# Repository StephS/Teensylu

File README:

UPDATE: TeensyluV1 is a complete redesign of the board. I have moved the power connector closer to the mosfets. Pins have changed! This new board is slightly larger than the older versions - It now matches the size of the Teensylu2
The hotend and bed connectors have changed to high power connectors. The main power connector can either be  screw connector, or a 6-Pin ATX-PCIE power connector. Please note the orientation of the connector and the polarity! Do not use the older 4 pin ATX connector!!!
It is highly recommended that this board is built using 2oz-in copper. Less than that may lead to board damage or FIRE!
I recommend a 15 Amp fuse in the mini-blade fuse holder.

I do not recommend using the older teensylu boards, get the TeensyluV1 board and use the added safety features.

I have decided to release 2 different versions of the board, The 2 Layer version, and 4 Layer version. The 4 layer version has greater power capacity due to uninterrupted power planes. The 2 layer version will be cheaper to manufacture. Functionally the boards are identical. I would prefer the 4 layer version, but I realize that COST is a major issue (up to 3 times the cost to manufacture 4 layer versus 2 layer).

As with all hobbiest electronics, there is a certain degree of risk involved. I had hoped that by making this project open source, that users would provide feedback and improvements to the design.
This has not happened.

Again, Use this board at your own risk!
I am releasing these designs without warranty or guarantee.

There is no such thing as a "Safe" 3d printer controller. Keep a smoke detector nearby and have a fire extinguisher handy. Do NOT the leave unattended. Disconnect from power source when not in use.

http://reprap.org/wiki/Teensylu

If you'd like to donate so I can buy the full version of Eagle, and make more cool stuff, please contact me through Google+ at https://plus.google.com/+StephanieS3D

Disclaimer:
These designs are provided without any warrenty, expressed or implied. This is a prototype designed for hobbiest use only.
Care should be taken during use and appropriate safety precautions taken.
The author is providing this item "as is". The author does not provide any warranty of the item whatsoever, whether express, implied, or statutory, including, but not limited to, any warranty of merchantability or fitness for a particular purpose or any warranty that the contents of the item will be error-free.
In no respect shall the author incur any liability for any damages, including, but limited to, direct, indirect, special, or consequential damages arising out of, resulting from, or any way connected to the use of the item, whether or not based upon warranty, contract, tort, or otherwise; whether or not injury was sustained by persons or property or otherwise; and whether or not loss was sustained from, or arose out of, the results of, the item, or any services that may be provided by the author.

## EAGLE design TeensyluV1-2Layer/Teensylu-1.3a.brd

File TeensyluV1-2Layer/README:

Version 1.3 is ready for production, earlier versions should not be used.
This version is a 2 Layer board designed for low cost manufacturing. A 4 Layer board is also available.
It is required that the top and bottom layers be 2oz/in.
24v power supply should be possible, please note to use a 24v heat bed, hotend, and fans or else damage or FIRE can occur.

Assembly notes:
J1-J7 are 22ga Solid core wire jumpers at 0.1" spacing. Do not attempt to stuff with headers.
J13 and J15 occupy the same space. Choose an appropriate header for the target system.

Please see TeensyluV1_Pin_Mapping.txt for the correct pin mapping using the teensyduino library. Analog pins should use the analog pin reference.

The BOM is included. Please use parts of the same or higher ratings.

If you'd like to donate so I can buy the full version of Eagle, and make more cool stuff, please contact me through Google+ at https://plus.google.com/+StephanieS3D

Disclaimer:
These designs are provided without any warrenty, expressed or implied. This is a prototype designed for hobbiest use only.
Care should be taken during use and appropriate safety precautions taken.
The author is providing this item "as is". The author does not provide any warranty of the item whatsoever, whether express, implied, or statutory, including, but not limited to, any warranty of merchantability or fitness for a particular purpose or any warranty that the contents of the item will be error-free.
In no respect shall the author incur any liability for any damages, including, but limited to, direct, indirect, special, or consequential damages arising out of, resulting from, or any way connected to the use of the item, whether or not based upon warranty, contract, tort, or otherwise; whether or not injury was sustained by persons or property or otherwise; and whether or not loss was sustained from, or arose out of, the results of, the item, or any services that may be provided by the author.

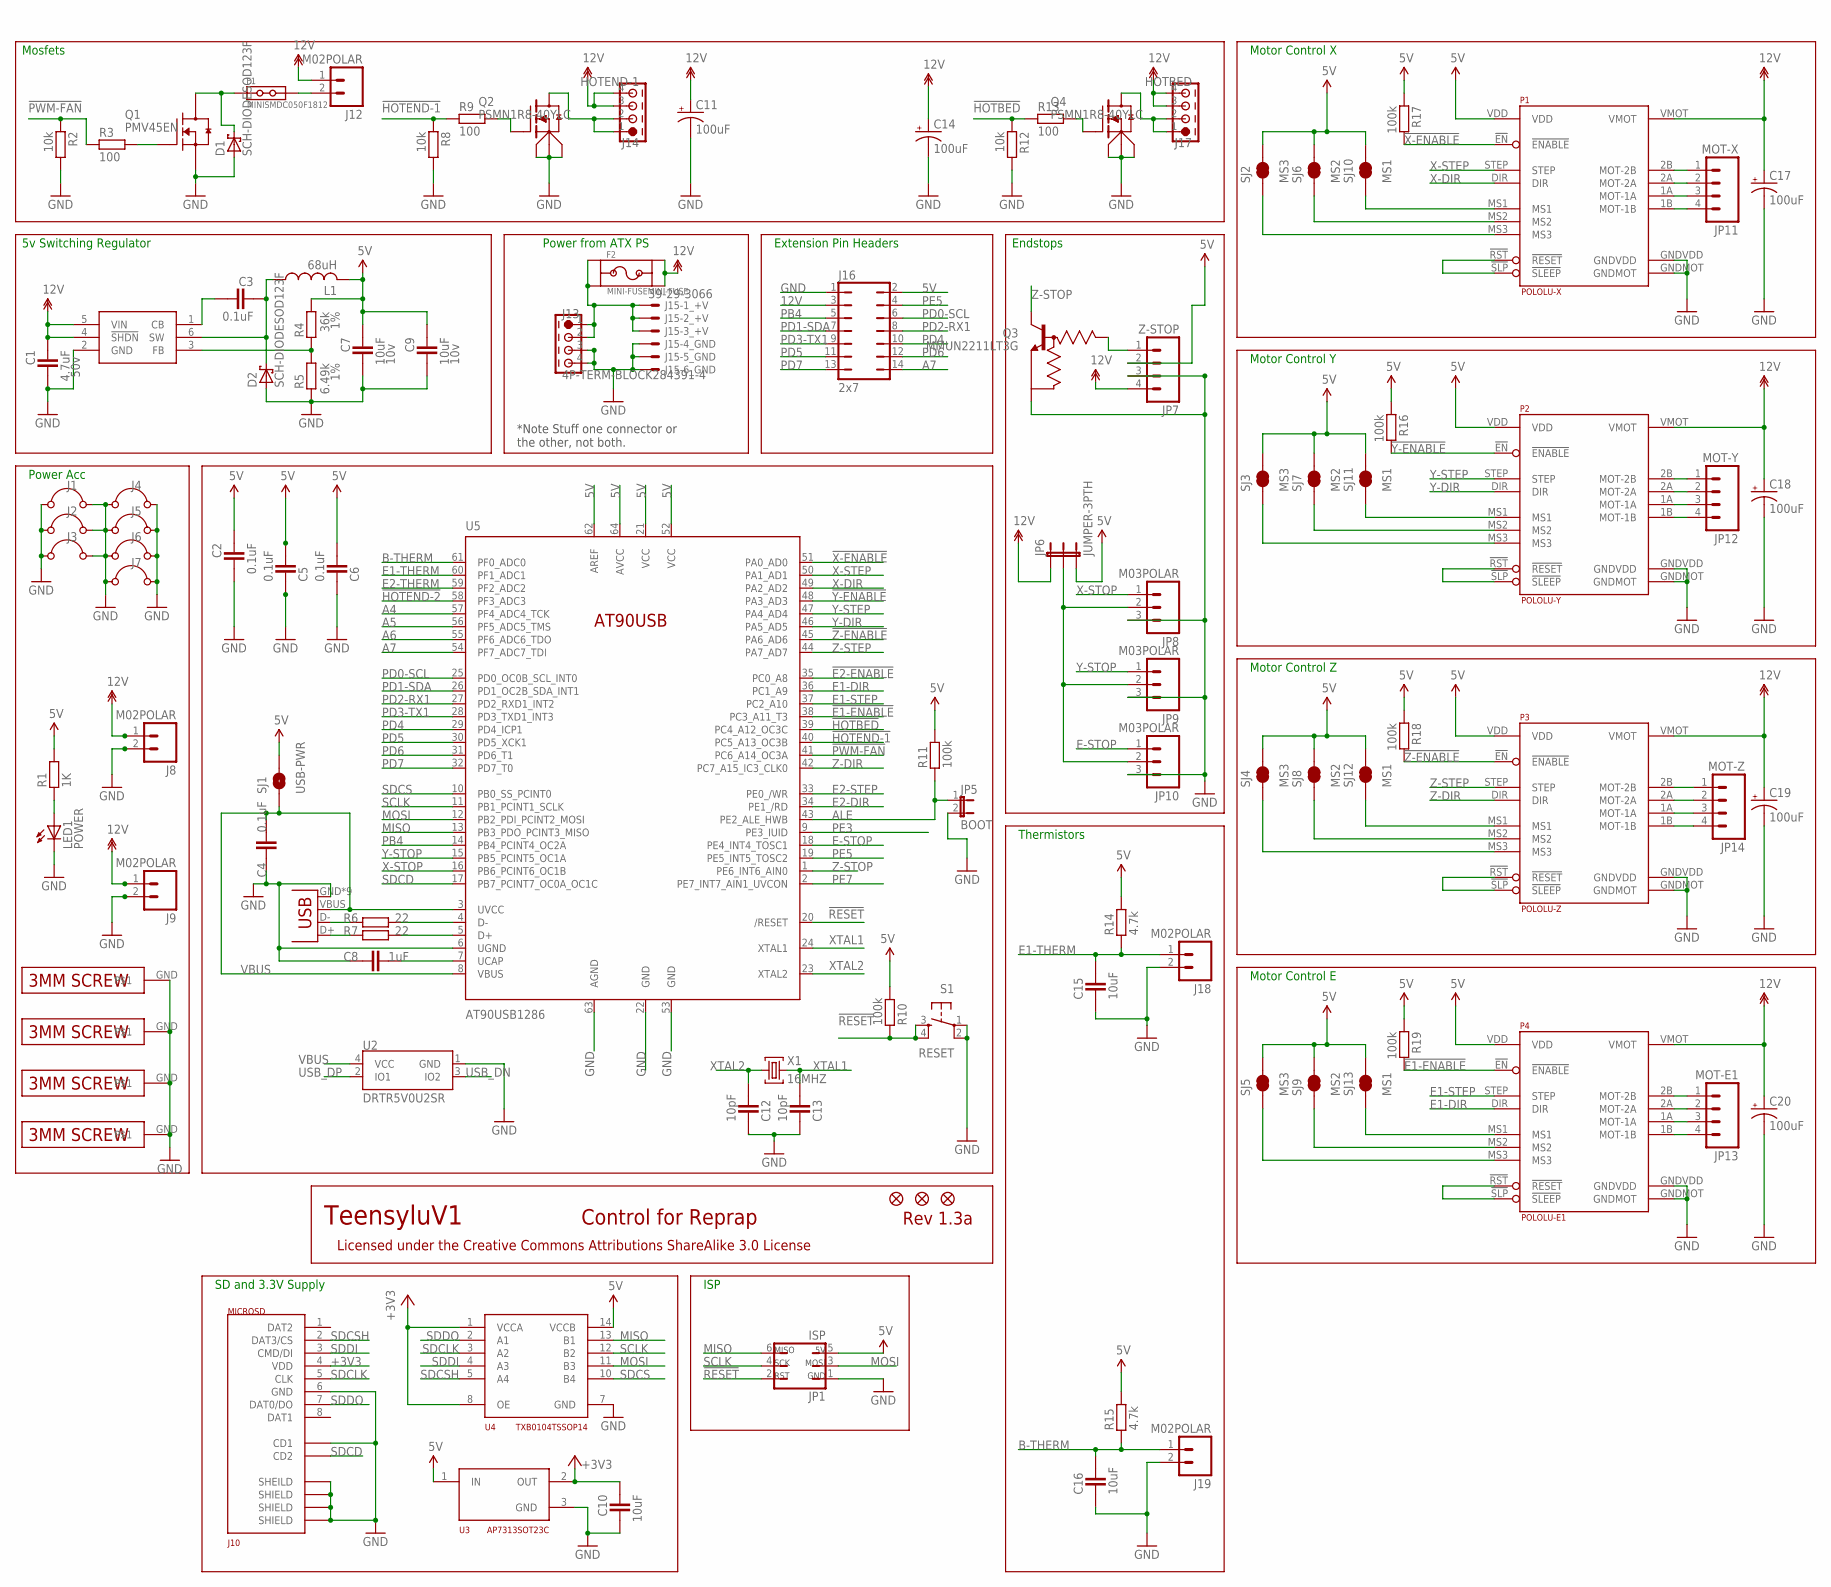
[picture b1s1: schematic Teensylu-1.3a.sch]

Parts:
C1: 4.7uF; CAPC3215X168N; TOLERANCE 10%; MANUFACTURER_PART_NUMBER UMK316AB7475KL-T
C2, C4, C5, C6: 0.1uF; CAPC1608X92N; TOLERANCE 10%; MANUFACTURER_PART_NUMBER GRM188R71C104KA01D
C3: 0.1uF; CAPC1608X92N; TOLERANCE 10%; MANUFACTURER_PART_NUMBER CL10B104KB8NNNC
C7, C9: 10uF; CAPC2012X145AN; TOLERANCE 10%; MANUFACTURER_PART_NUMBER GRM21BR71A106KE51L
C8: 1uF; CAPC1608X92N; TOLERANCE 20%; MANUFACTURER_PART_NUMBER CL10A105MO8NNNC
C10, C15, C16: 10uF; CAPC1608X92N; TOLERANCE 20%; MANUFACTURER_PART_NUMBER GRM188R61C106MA73D
C11, C14, C17, C18, C19, C20: 100uF; PANASONIC_D; TOLERANCE 20%; MANUFACTURER_PART_NUMBER EEE-FTH101XAP
C12, C13: 10pF; CAPC1608X92N; TOLERANCE 5%; MANUFACTURER_PART_NUMBER CL10C100JB8NCNC
D1: SCH-DIODESOD123F; SOD123F
D2: SCH-DIODESOD123F; SOD123F; MANUFACTURER_PART_NUMBER PMEG4010CEH,115
F1: MINISMDC050F1812; MINISMDC
F2: MINI-FUSEMINI-FUSE; MINI_FUSE
J1, J2, J3, J4, J5, J6, J7: 22ga; WJ_01_08; MANUFACTURER_PART_NUMBER N/A
J8, J9, J12, J18, J19: M02POLAR; MOLEX-1X2; MANUFACTURER_PART_NUMBER 0022272021
J10: MICROSD; AMPHENOL-MICROSD
J11: USB-MICRO-PTH; USB-MICROB-PTH
J13: 4P-TERM-BLOCK284391-4; 284391-4
J14: HOTEND-1; 284391-4
J15: 39-29-3066
J16: 2x7; JP7Q; MANUFACTURER_PART_NUMBER M20-9980746
J17: HOTBED; 284391-4
JP1: ISP
JP2, JP3, JP4: FIDUCIAL1X2.5; FIDUCIAL-1X2.5
JP5: BOOT; 1X02; MANUFACTURER_PART_NUMBER M20-9990246
JP6: JUMPER-3PTH; 1X03
JP7: Z-STOP; MOLEX-1X4
JP8, JP9, JP10: M03POLAR; MOLEX-1X3; MANUFACTURER_PART_NUMBER 0022272031
JP11: MOT-X; MOLEX-1X4
JP12: MOT-Y; MOLEX-1X4
JP13: MOT-E1; MOLEX-1X4
JP14: MOT-Z; MOLEX-1X4
L1: 68uH; SRN6045; MANUFACTURER_PART_NUMBER SRN6045-680M
LED1: POWER; CHIPLED_0805; MANUFACTURER_PART_NUMBER APT2012SGC
P1: POLOLU-X; POLOLU-STEPPER-PTH
P2: POLOLU-Y; POLOLU-STEPPER-PTH
P3: POLOLU-Z; POLOLU-STEPPER-PTH
P4: POLOLU-E1; POLOLU-STEPPER-PTH
Q1: PMV45EN; SOT23C; VOLTAGE 60V; MANUFACTURER_PART_NUMBER IRLML2060TRPBF
Q2, Q4: PSMN1R8-40YLC; LFPACK-POWERPAK-SO8
Q3: MMUN2211LT3G; SOT23C; MANUFACTURER_PART_NUMBER MMUN2211LT3G
R1: 1K; RESC1608X55N
R2, R8, R12: 10k; RESC1608X55N
R3, R9, R13: 100; RESC1608X55N
R4: 36k; RESC1608X55N; TOLERANCE 1%
R5: 6.49k; RESC1608X55N; TOLERANCE 1%
R6, R7: 22; RESC1608X55N
R10, R11, R16, R17, R18, R19: 100k; RESC1608X55N
R14, R15: 4.7k; RESC1608X55N
S1: RESET; TACTILE_SWITCH_SMD
SCREW1, SCREW2, SCREW3, SCREW4: 3MM-SCREW; PLATEDSCREW
SJ1: USB-PWR; SJ_2S-NO
SJ2, SJ3, SJ4, SJ5: MS3; SJ_2S-TRACE
SJ6, SJ7, SJ8, SJ9: MS2; SJ_2S-TRACE
SJ10, SJ11, SJ12, SJ13: MS1; SJ_2S-TRACE
U1: LMR16006X; TSOT6
U2: DRTR5V0U2SR; SOT143-R
U3: AP7313SOT23C; SOT23C
U4: TXB0104TSSOP14; TSSOP14
U5: AT90USB1286; TQFP64-2; MANUFACTURER_PART_NUMBER AT90USB1286
X1: 16MHZ; NDK-XTAL; MANUFACTURER_PART_NUMBER NX5032GA-16.000000MHZ-LN-CD-1

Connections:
5V: C2.1, C5.2, C6.2, C7.1, C9.1, J16.2, JP1.5, JP6.3, JP7.2, L1.2, P1.VDD, P2.VDD, P3.VDD, P4.VDD, R1.2, R4.1, R10.2, R11.2, R14.2, R15.2, R16.1, R17.1, R18.1, R19.1, SJ1.2, SJ2.2, SJ3.2, SJ4.2, SJ5.2, SJ6.2, SJ7.2, SJ8.2, SJ9.2, SJ10.2, SJ11.2, SJ12.2, SJ13.2, U3.1 (IN), U4.14 (VCCB), U5.21 (VCC), U5.52 (VCC), U5.62 (AREF), U5.64 (AVCC)
5VREG_CB: C3.2, U1.1 (CB)
5VREG_FB: R4.2, R5.1, U1.3 (FB)
5VREG_SW: C3.1, D2.C, L1.1, U1.6 (SW)
12V: C1.1, C11.+, C14.+, C17.+, C18.+, C19.+, C20.+, F2.P$3, F2.P$4, J8.1, J9.1, J12.1, J14.3, J14.4, J16.3, J17.3, J17.4, JP6.1, JP7.4, P1.VMOT, P2.VMOT, P3.VMOT, P4.VMOT, U1.4 (!SHDN), U1.5 (VIN)
12V_FUSE: F2.P$1, F2.P$2, J13.1, J13.2, J15.1, J15.2, J15.3
!E1-ENABLE: P4.!EN (!ENABLE), R19.2, U5.38 (PC3_A11_T3)
!E2-ENABLE: U5.35 (PC0_A8)
!HOTBED: R12.1, R13.1, U5.39 (PC4_A12_OC3C)
!HOTEND-1: R8.1, R9.1, U5.40 (PC5_A13_OC3B)
!HOTEND-2: U5.58 (PF3_ADC3)
!PWM-FAN: R2.1, R3.1, U5.41 (PC6_A14_OC3A)
!RESET: JP1.2, R10.1, S1.3, S1.4, U5.20 (/RESET)
!X-ENABLE: P1.!EN (!ENABLE), R17.2, U5.51 (PA0_AD0)
!Y-ENABLE: P2.!EN (!ENABLE), R16.2, U5.48 (PA3_AD3)
!Z-ENABLE: P3.!EN (!ENABLE), R18.2, U5.45 (PA6_AD6)
+3V3: C10.1, J10.4 (VDD), U3.2 (OUT), U4.1 (VCCA), U4.8 (OE)
A4: U5.57 (PF4_ADC4_TCK)
A5: U5.56 (PF5_ADC5_TMS)
A6: U5.55 (PF6_ADC6_TDO)
A7: J16.14, U5.54 (PF7_ADC7_TDI)
ALE: JP5.1, R11.1, U5.43 (PE2_ALE_HWB)
B-THERM: C16.2, J19.1, R15.1, U5.61 (PF0_ADC0)
E1-DIR: P4.DIR, U5.36 (PC1_A9)
E1-STEP: P4.STEP, U5.37 (PC2_A10)
E1-THERM: C15.2, J18.1, R14.1, U5.60 (PF1_ADC1)
E2-DIR: U5.34 (PE1_/RD)
E2-STEP: U5.33 (PE0_/WR)
E2-THERM: U5.59 (PF2_ADC2)
E-MOT-1A: JP13.3, P4.1A (MOT-1A)
E-MOT-1B: JP13.4, P4.1B (MOT-1B)
E-MOT-2A: JP13.2, P4.2A (MOT-2A)
E-MOT-2B: JP13.1, P4.2B (MOT-2B)
E-MS1: P4.MS1, SJ13.1
E-MS2: P4.MS2, SJ9.1
E-MS3: P4.MS3, SJ5.1
E-RESETSLEEP: P4.!RST (!RESET), P4.!SLP (!SLEEP)
E-STOP: JP10.1, U5.18 (PE4_INT4_TOSC1)
ENDSTOP+V: JP6.2, JP8.2, JP9.2, JP10.2
GND: C1.2, C2.2, C4.1, C5.1, C6.1, C7.2, C8.1, C9.2, C10.2, C11.-, C12.1, C13.1, C14.-, C15.1, C16.1, C17.-, C18.-, C19.-, C20.-, D1.A, D2.A, J1.1 (+), J1.2 (-), J2.1 (+), J2.2 (-), J3.1 (+), J3.2 (-), J4.1 (+), J4.2 (-), J5.1 (+), J5.2 (-), J6.1 (+), J6.2 (-), J7.1 (+), J7.2 (-), J8.2, J9.2, J10.6 (GND), J10.C1 (SHEILD), J10.C2 (SHIELD), J10.C3 (SHIELD), J10.C4 (SHIELD), J10.CD1, J11.GND, J11.GND1 (GND), J11.GND2 (GND), J11.GND3 (GND), J11.GND4 (GND), J11.GND5 (GND), J11.GND6 (GND), J11.GND7 (GND), J11.GND8 (GND), J13.3, J13.4, J15.4, J15.5, J15.6, J16.1, J18.2, J19.2, JP1.1, JP5.2, JP7.3, JP8.3, JP9.3, JP10.3, LED1.C, P1.GNDMOT, P1.GNDVDD, P2.GNDMOT, P2.GNDVDD, P3.GNDMOT, P3.GNDVDD, P4.GNDMOT, P4.GNDVDD, Q1.2 (S), Q2.1 (S1), Q2.2 (S2), Q2.3 (S3), Q3.2 (E), Q4.1 (S1), Q4.2 (S2), Q4.3 (S3), R2.2, R5.2, R8.2, R12.2, S1.1, S1.2, SCREW1.GND, SCREW2.GND, SCREW3.GND, SCREW4.GND, U1.2 (GND), U2.1 (GND), U3.3 (GND), U4.7 (GND), U5.6 (UGND), U5.22 (GND), U5.53 (GND), U5.63 (AGND)
HOTBED-GND: J17.1, J17.2, Q4.5-8 (D)
HOTEND-GND: J14.1, J14.2, Q2.5-8 (D)
MISO: JP1.6, U4.13 (B1), U5.13 (PB3_PDO_PCINT3_MISO)
MOSI: JP1.3, U4.11 (B3), U5.12 (PB2_PDI_PCINT2_MOSI)
unnamed: LED1.A, R1.1
unnamed: Q4.4 (G), R13.2
unnamed: R6.2, U5.4 (D-)
unnamed: R7.2, U5.5 (D+)
unnamed: F1.P$2, J12.2
unnamed: D1.C, F1.P$1, Q1.3 (D)
unnamed: Q1.1 (G), R3.2
unnamed: Q2.4 (G), R9.2
PB4: J16.5, U5.14 (PB4_PCINT4_OC2A)
PD0-SCL: J16.6, U5.25 (PD0_OC0B_SCL_INT0)
PD1-SDA: J16.7, U5.26 (PD1_OC2B_SDA_INT1)
PD2-RX1: J16.8, U5.27 (PD2_RXD1_INT2)
PD3-TX1: J16.9, U5.28 (PD3_TXD1_INT3)
PD4: J16.10, U5.29 (PD4_ICP1)
PD5: J16.11, U5.30 (PD5_XCK1)
PD6: J16.12, U5.31 (PD6_T1)
PD7: J16.13, U5.32 (PD7_T0)
PE3: U5.9 (PE3_IUID)
PE5: J16.4, U5.19 (PE5_INT5_TOSC2)
PE7: U5.2 (PE7_INT7_AIN1_UVCON)
SCLK: JP1.4, U4.12 (B2), U5.11 (PB1_PCINT1_SCLK)
SDCD: J10.CD2, U5.17 (PB7_PCINT7_OC0A_OC1C)
SDCLK: J10.5 (CLK), U4.3 (A2)
SDCS: U4.10 (B4), U5.10 (PB0_SS_PCINT0)
SDCSH: J10.2 (DAT3/CS), U4.5 (A4)
SDDI: J10.3 (CMD/DI), U4.4 (A3)
SDDO: J10.7 (DAT0/DO), U4.2 (A1)
UCAP: C8.2, U5.7 (UCAP)
USB_DN: J11.D-, R6.1, U2.3 (IO2)
USB_DP: J11.D+, R7.1, U2.2 (IO1)
VBUS: C4.2, J11.VBUS, SJ1.1, U2.4 (VCC), U5.3 (UVCC), U5.8 (VBUS)
X-DIR: P1.DIR, U5.49 (PA2_AD2)
X-MOT-1A: JP11.3, P1.1A (MOT-1A)
X-MOT-1B: JP11.4, P1.1B (MOT-1B)
X-MOT-2A: JP11.2, P1.2A (MOT-2A)
X-MOT-2B: JP11.1, P1.2B (MOT-2B)
X-MS1: P1.MS1, SJ10.1
X-MS2: P1.MS2, SJ6.1
X-MS3: P1.MS3, SJ2.1
X-RESETSLEEP: P1.!RST (!RESET), P1.!SLP (!SLEEP)
X-STEP: P1.STEP, U5.50 (PA1_AD1)
X-STOP: JP8.1, U5.16 (PB6_PCINT6_OC1B)
XTAL1: C13.2, U5.24 (XTAL1), X1.P$2 (2)
XTAL2: C12.2, U5.23 (XTAL2), X1.P$1 (1)
Y-DIR: P2.DIR, U5.46 (PA5_AD5)
Y-MOT-1A: JP12.3, P2.1A (MOT-1A)
Y-MOT-1B: JP12.4, P2.1B (MOT-1B)
Y-MOT-2A: JP12.2, P2.2A (MOT-2A)
Y-MOT-2B: JP12.1, P2.2B (MOT-2B)
Y-MS1: P2.MS1, SJ11.1
Y-MS2: P2.MS2, SJ7.1
Y-MS3: P2.MS3, SJ3.1
Y-RESETSLEEP: P2.!RST (!RESET), P2.!SLP (!SLEEP)
Y-STEP: P2.STEP, U5.47 (PA4_AD4)
Y-STOP: JP9.1, U5.15 (PB5_PCINT5_OC1A)
Z-DIR: P3.DIR, U5.42 (PC7_A15_IC3_CLK0)
Z-MOT-1A: JP14.3, P3.1A (MOT-1A)
Z-MOT-1B: JP14.4, P3.1B (MOT-1B)
Z-MOT-2A: JP14.2, P3.2A (MOT-2A)
Z-MOT-2B: JP14.1, P3.2B (MOT-2B)
Z-MS1: P3.MS1, SJ12.1
Z-MS2: P3.MS2, SJ8.1
Z-MS3: P3.MS3, SJ4.1
Z-RESETSLEEP: P3.!RST (!RESET), P3.!SLP (!SLEEP)
Z-STEP: P3.STEP, U5.44 (PA7_AD7)
Z-STOP: Q3.3 (C), U5.1 (PE6_INT6_AIN0)
Z-STOP-BIAS: JP7.1, Q3.1 (B)

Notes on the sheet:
Motor Control X
Motor Control Y
Motor Control Z
Motor Control E
ISP
Thermistors
Endstops
Mosfets
Power Acc
TeensyluV1
Rev 1.3a
Control for Reprap
Licensed under the Creative Commons Attributions ShareAlike 3.0 License
Extension Pin Headers
Power from ATX PS
5v Switching Regulator
SD and 3.3V Supply
*Note Stuff one connector or the other, not both.

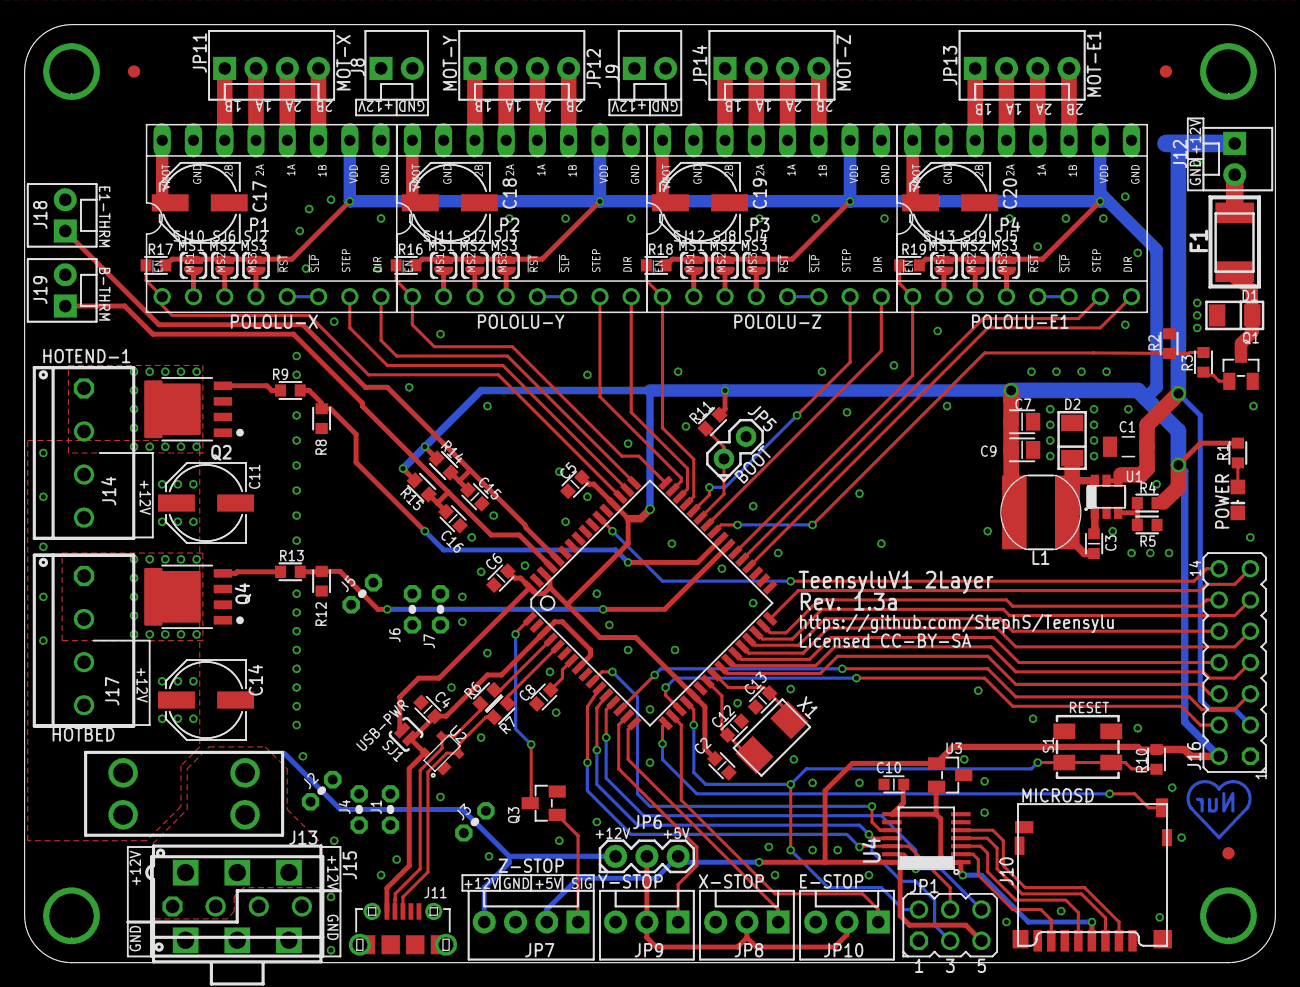
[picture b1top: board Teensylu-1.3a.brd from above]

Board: 2 copper layers, 101.6 x 76.2 mm, 110 parts (0 on the bottom side), 101 nets.

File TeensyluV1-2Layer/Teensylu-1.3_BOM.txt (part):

Part   Value                 Device                     Package             Description                                                                   CURRENT DCR   DESCRIPTION                               ESR    INDUCTANCE IRMS MANUFACTURER            MANUFACTURER_PART_NUMBER      NOTES                                                                       RDS_ON   REVERSE_VOLTAGE TOLERANCE VDC VGS   VOLTAGE VOLTAGE_OUTPUT
C1     4.7uF                 CAPACITOR_1206             CAPC3215X168N                                                                                                                                                                    Yaiyo Yuden             UMK316AB7475KL-T                                                                                                                   10%       50v                             
C2     0.1uF                 CAPACITOR_0603             CAPC1608X92N                                                                                                                                                                     Murata                  GRM188R71C104KA01D                                                                                                                 10%       16V                             
C3     0.1uF                 CAPACITOR_0603             CAPC1608X92N                                                                                                                                                                     Samsung                 CL10B104KB8NNNC                                                                                                                    10%       50V                             
C4     0.1uF                 CAPACITOR_0603             CAPC1608X92N                                                                                                                                                                     Murata                  GRM188R71C104KA01D                                                                                                                 10%       16V                             
C5     0.1uF                 CAPACITOR_0603             CAPC1608X92N                                                                                                                                                                     Murata                  GRM188R71C104KA01D                                                                                                                 10%       16V                             
C6     0.1uF                 CAPACITOR_0603             CAPC1608X92N                                                                                                                                                                     Murata                  GRM188R71C104KA01D                                                                                                                 10%       16V                             
C7     10uF                  CAPACITOR_0805             CAPC2012X145AN                                                                                                                                            0.0030                 Murata                  GRM21BR71A106KE51L                                                                                                                 10%       10v                             
C8     1uF                   CAPACITOR_0603             CAPC1608X92N                                                                                                                                                                     Samsung                 CL10A105MO8NNNC                                                                                                                    20%       16V                             
C9     10uF                  CAPACITOR_0805             CAPC2012X145AN                                                                                                                                            0.0030                 Murata                  GRM21BR71A106KE51L                                                                                                                 10%       10v                             
C10    10uF                  CAPACITOR_0603             CAPC1608X92N                                                                                                                                                                     Murata                  GRM188R61C106MA73D                                                                                                                 20%       16V                             
C11    100uF                 CPOL-USD                   PANASONIC_D         POLARIZED CAPACITOR, American symbol                                                                                                                         Panasonic               EEE-FTH101XAP                                                                                                                      20%       50v                             
C12    10pF                  CAPACITOR_0603             CAPC1608X92N                                                                                                                                                                     Samsung                 CL10C100JB8NCNC                                                                                                                    5%        50V                             
C13    10pF                  CAPACITOR_0603             CAPC1608X92N                                                                                                                                                                     Samsung                 CL10C100JB8NCNC                                                                                                                    5%        50V                             
C14    100uF                 CPOL-USD                   PANASONIC_D         POLARIZED CAPACITOR, American symbol                                                                                                                         Panasonic               EEE-FTH101XAP                                                                                                                      20%       50v                             
C15    10uF                  CAPACITOR_0603             CAPC1608X92N                                                                                                                                                                     Murata                  GRM188R61C106MA73D                                                                                                                 20%       16V                             
C16    10uF                  CAPACITOR_0603             CAPC1608X92N                                                                                                                                                                     Murata                  GRM188R61C106MA73D                                                                                                                 20%       16V                             
C17    100uF                 CPOL-USD                   PANASONIC_D         POLARIZED CAPACITOR, American symbol                                                                                                                         Panasonic               EEE-FTH101XAP                                                                                                                      20%       50v                             
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
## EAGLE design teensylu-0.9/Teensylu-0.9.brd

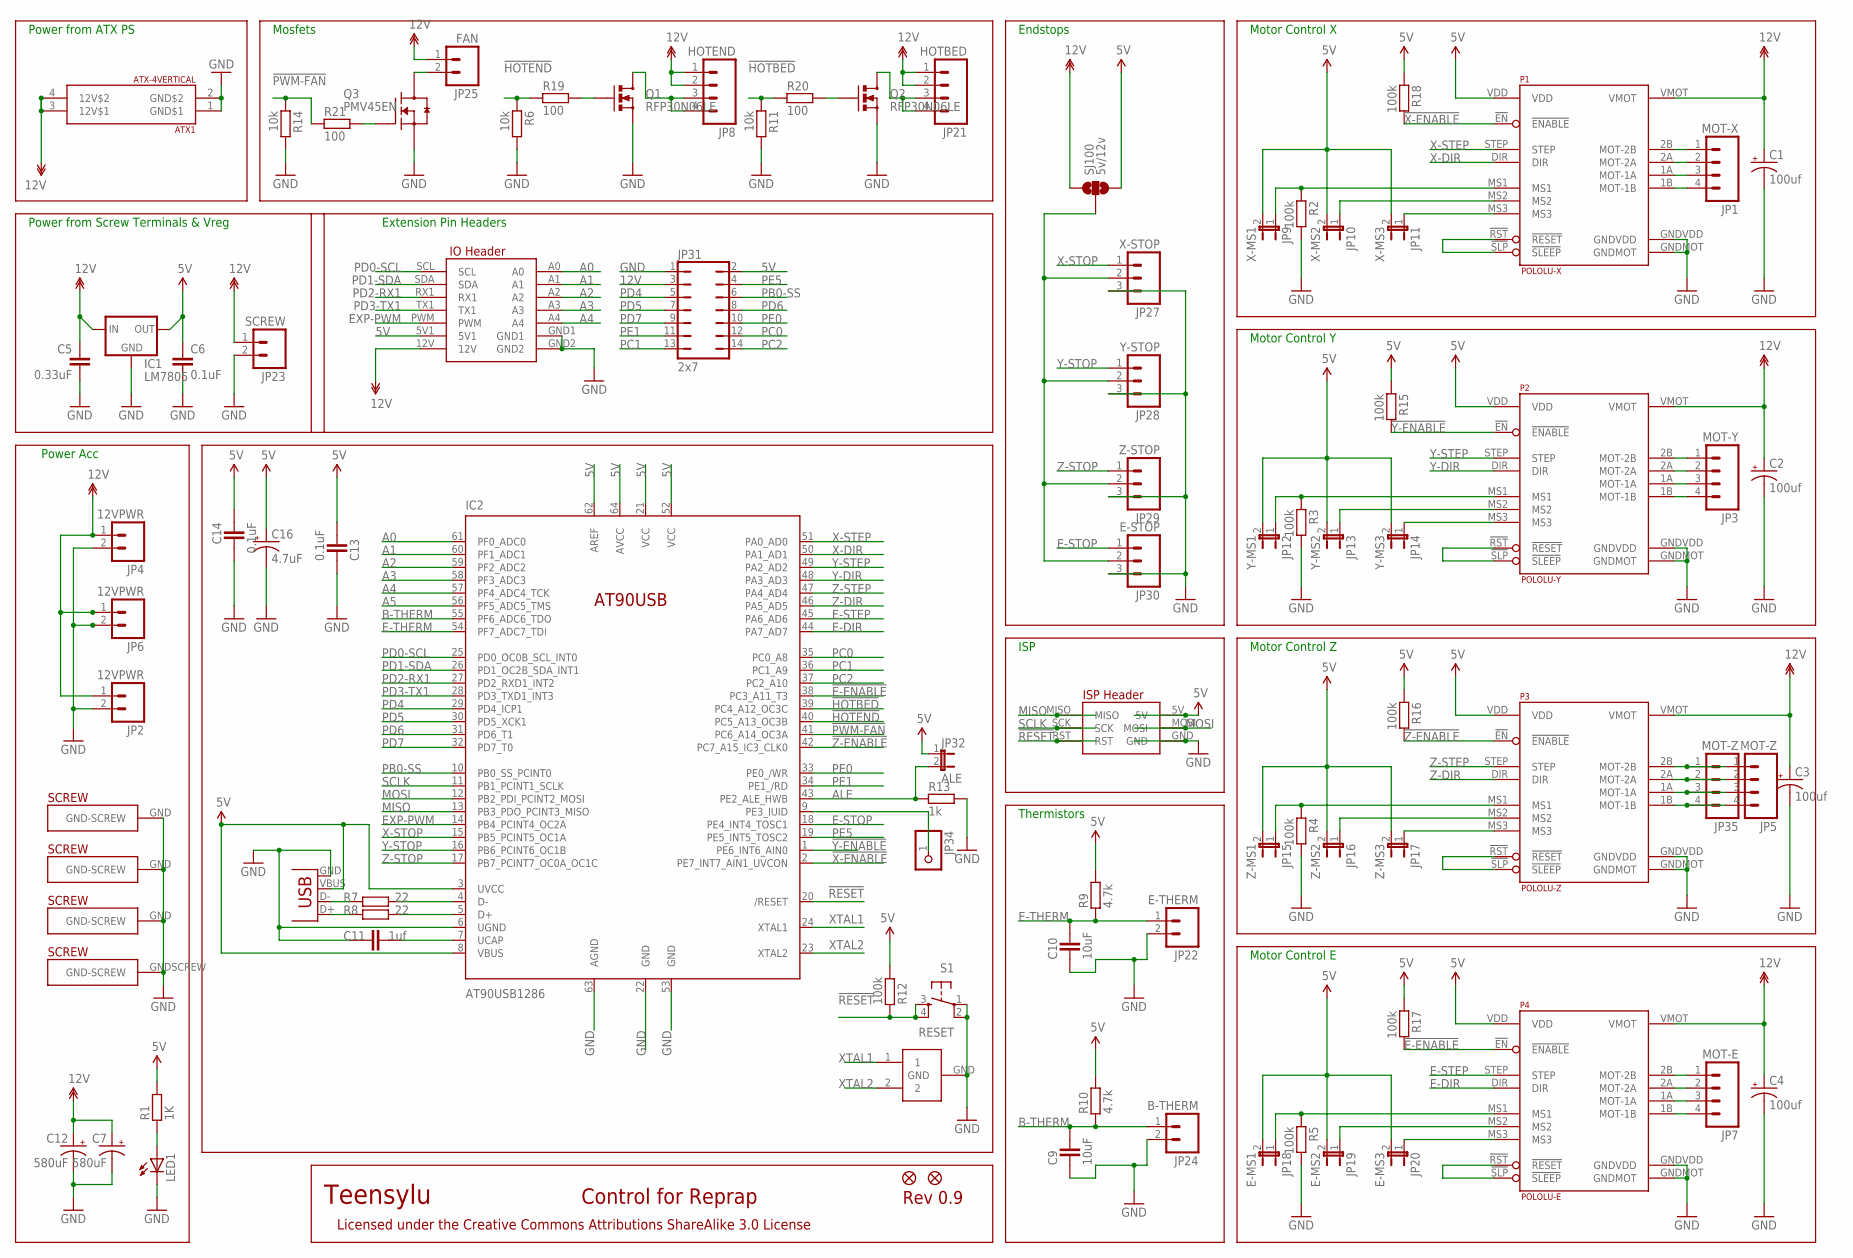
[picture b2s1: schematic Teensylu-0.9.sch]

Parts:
ATX1: ATX-4VERTICAL; MINIFITJR-4-VERTICAL
C1, C2, C3, C4: 100uf; CPOL-RADIAL-100UF-25V
C5: 0.33uF; CAP-PTH-SMALL2
C6: 0.1uF; CAP-PTH-SMALL2
C7, C12: 580uF; CPOL-RADIAL-1000UF-25V
C9, C10: 10uF; CAPC1608X92N
C11: 1uf; CAPC1608X92N
C13, C14: 0.1uF; CAPC1608X92N
C16: 4.7uF; CPOL-RADIAL-10UF-25V
IC1: LM7805; 78XXL-CUSTOM
IC2: AT90USB1286; TQFP64-2
J1: USB; USB-B-PTH
JP1: MOT-X; MOLEX-1X4
JP2, JP4, JP6: 12VPWR; MOLEX-1X2
JP3: MOT-Y; MOLEX-1X4
JP5, JP35: MOT-Z; MOLEX-1X4
JP7: MOT-E; MOLEX-1X4
JP8: HOTEND; MOLEX-1X4
JP9: X-MS1; 1X02
JP10: X-MS2; 1X02
JP11: X-MS3; 1X02
JP12: Y-MS1; 1X02
JP13: Y-MS2; 1X02
JP14: Y-MS3; 1X02
JP15: Z-MS1; 1X02
JP16: Z-MS2; 1X02
JP17: Z-MS3; 1X02
JP18: E-MS1; 1X02
JP19: E-MS2; 1X02
JP20: E-MS3; 1X02
JP21: HOTBED; MOLEX-1X4
JP22: E-THERM; 1X02
JP23: SCREW; SCREWTERMINAL-5MM-2
JP24: B-THERM; 1X02
JP25: FAN; 1X02
JP26, JP33: FIDUCIAL1X2.5; FIDUCIAL-1X2.5
JP27: X-STOP; MOLEX-1X3
JP28: Y-STOP; MOLEX-1X3
JP29: Z-STOP; MOLEX-1X3
JP30: E-STOP; MOLEX-1X3
JP31: 2x7; JP7Q
JP32: ALE; 1X02
JP34: PINHD-1X1; 1X01
LED1: LED5MM
P1: POLOLU-X; POLOLU-ALLEGRO-PTH
P2: POLOLU-Y; POLOLU-ALLEGRO-PTH
P3: POLOLU-Z; POLOLU-ALLEGRO-PTH
P4: POLOLU-E; POLOLU-ALLEGRO-PTH
Q1, Q2: RFP30N06LE; TO220V
Q3: PMV45EN; SOT95P280X135-3N
R1: 1K; RESC1608X55N
R2, R3, R4, R5, R12, R15, R16, R17, R18: 100k; RESC1608X55N
R6, R11, R14: 10k; RESC1608X55N
R7, R8: 22; RESC1608X55N
R9, R10: 4.7k; RESC1608X55N
R13: 1k; RESC1608X55N
R19, R20, R21: 100; RESC1608X55N
S1: RESET; TACTILE-PTH
SJ100: 5v/12v; SJ_2W
U$17, U$24, U$37: PLATED-SCREW; PLATEDSCREW
U$34: IO_HEADERS_SCREW; IO_HEADER-PLATEDSCREW
XTAL: KYOCERA_PQRC_TYPE_S_RESONATOR; AVX_3.2X1.3_RESONATOR

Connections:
5V: C6.1, C13.2, C14.1, C16.1 (+), IC1.OUT, IC2.3 (UVCC), IC2.8 (VBUS), IC2.21 (VCC), IC2.52 (VCC), IC2.62 (AREF), IC2.64 (AVCC), J1.VBUS, JP9.2, JP10.2, JP11.2, JP12.2, JP13.2, JP14.2, JP15.2, JP16.2, JP17.2, JP18.2, JP19.2, JP20.2, JP31.2, JP32.1, P1.VDD, P2.VDD, P3.VDD, P4.VDD, R1.2, R9.2, R10.2, R12.2, R15.1, R16.1, R17.1, R18.1, SJ100.3, U$34.5V, U$34.5V1
12V: ATX1.3 (12V$1), ATX1.4 (12V$2), C1.1 (+), C2.1 (+), C3.1 (+), C4.1 (+), C5.1, C7.1 (+), C12.1 (+), IC1.IN, JP2.1, JP4.1, JP6.1, JP8.1, JP8.2, JP21.1, JP21.2, JP23.1, JP25.1, JP31.3, P1.VMOT, P2.VMOT, P3.VMOT, P4.VMOT, SJ100.1, U$34.12V
!E-ENABLE: IC2.38 (PC3_A11_T3), P4.!EN (!ENABLE), R17.2
!HOTBED: IC2.39 (PC4_A12_OC3C), R11.1, R20.1
!HOTEND: IC2.40 (PC5_A13_OC3B), R6.1, R19.1
!PWM-FAN: IC2.41 (PC6_A14_OC3A), R14.1, R21.1
!RESET: IC2.20 (/RESET), R12.1, S1.3, S1.4, U$34.RST
!X-ENABLE: IC2.2 (PE7_INT7_AIN1_UVCON), P1.!EN (!ENABLE), R18.2
!Y-ENABLE: IC2.1 (PE6_INT6_AIN0), P2.!EN (!ENABLE), R15.2
!Z-ENABLE: IC2.42 (PC7_A15_IC3_CLK0), P3.!EN (!ENABLE), R16.2
A0: IC2.61 (PF0_ADC0), U$34.A0
A1: IC2.60 (PF1_ADC1), U$34.A1
A2: IC2.59 (PF2_ADC2), U$34.A2
A3: IC2.58 (PF3_ADC3), U$34.A3
A4: IC2.57 (PF4_ADC4_TCK), U$34.A4
A5: IC2.56 (PF5_ADC5_TMS)
ALE: IC2.43 (PE2_ALE_HWB), JP32.2, R13.1
B-THERM: C9.2, IC2.55 (PF6_ADC6_TDO), JP24.1, R10.1
E-DIR: IC2.44 (PA7_AD7), P4.DIR
E-MOT-1A: JP7.3, P4.1A (MOT-1A)
E-MOT-1B: JP7.4, P4.1B (MOT-1B)
E-MOT-2A: JP7.2, P4.2A (MOT-2A)
E-MOT-2B: JP7.1, P4.2B (MOT-2B)
E-MS1: JP18.1, P4.MS1, R5.1
E-MS2: JP19.1, P4.MS2
E-MS3: JP20.1, P4.MS3
E-RESETSLEEP: P4.!RST (!RESET), P4.!SLP (!SLEEP)
E-STEP: IC2.45 (PA6_AD6), P4.STEP
E-STOP: IC2.18 (PE4_INT4_TOSC1), JP30.1
E-THERM: C10.2, IC2.54 (PF7_ADC7_TDI), JP22.1, R9.1
ENDSTOP+V: JP27.2, JP28.2, JP29.2, JP30.2, SJ100.2
EXP-PWM: IC2.14 (PB4_PCINT4_OC2A), U$34.PWM
GND: ATX1.1 (GND$1), ATX1.2 (GND$2), C1.2 (-), C2.2 (-), C3.2 (-), C4.2 (-), C5.2, C6.2, C7.2 (-), C9.1, C10.1, C11.1, C12.2 (-), C13.1, C14.2, C16.2 (-), IC1.GND, IC2.6 (UGND), IC2.22 (GND), IC2.53 (GND), IC2.63 (AGND), J1.GND, JP2.2, JP4.2, JP6.2, JP22.2, JP23.2, JP24.2, JP27.3, JP28.3, JP29.3, JP30.3, JP31.1, LED1.K (C), P1.GNDMOT, P1.GNDVDD, P2.GNDMOT, P2.GNDVDD, P3.GNDMOT, P3.GNDVDD, P4.GNDMOT, P4.GNDVDD, Q1.3 (S), Q2.3 (S), Q3.2 (S), R2.2, R3.2, R4.2, R5.2, R6.2, R11.2, R13.2, R14.2, S1.1, S1.2, U$17.GND, U$24.GND, U$34.GND, U$34.GND1, U$34.GND2, U$34.GNDSCREW (GND-SCREW), U$37.GND, XTAL.GND
HOTBED-GND: JP21.3, JP21.4, Q2.2 (D)
HOTEND-GND: JP8.3, JP8.4, Q1.2 (D)
MISO: IC2.13 (PB3_PDO_PCINT3_MISO), U$34.MISO
MOSI: IC2.12 (PB2_PDI_PCINT2_MOSI), U$34.MOSI
unnamed: LED1.A, R1.1
unnamed: J1.D-, R7.1
unnamed: IC2.4 (D-), R7.2
unnamed: IC2.5 (D+), R8.2
unnamed: J1.D+, R8.1
unnamed: JP25.2, Q3.3 (D)
unnamed: IC2.9 (PE3_IUID), JP34.1
unnamed: C11.2, IC2.7 (UCAP)
unnamed: Q3.1 (G), R21.2
unnamed: Q1.1 (G), R19.2
unnamed: Q2.1 (G), R20.2
PB0-SS: IC2.10 (PB0_SS_PCINT0), JP31.6
PC0: IC2.35 (PC0_A8), JP31.12
PC1: IC2.36 (PC1_A9), JP31.13
PC2: IC2.37 (PC2_A10), JP31.14
PD0-SCL: IC2.25 (PD0_OC0B_SCL_INT0), U$34.SCL
PD1-SDA: IC2.26 (PD1_OC2B_SDA_INT1), U$34.SDA
PD2-RX1: IC2.27 (PD2_RXD1_INT2), U$34.RX1
PD3-TX1: IC2.28 (PD3_TXD1_INT3), U$34.TX1
PD4: IC2.29 (PD4_ICP1), JP31.5
PD5: IC2.30 (PD5_XCK1), JP31.7
PD6: IC2.31 (PD6_T1), JP31.8
PD7: IC2.32 (PD7_T0), JP31.9
PE0: IC2.33 (PE0_/WR), JP31.10
PE1: IC2.34 (PE1_/RD), JP31.11
PE5: IC2.19 (PE5_INT5_TOSC2), JP31.4
SCLK: IC2.11 (PB1_PCINT1_SCLK), U$34.SCK
X-DIR: IC2.50 (PA1_AD1), P1.DIR
X-MOT-1A: JP1.3, P1.1A (MOT-1A)
X-MOT-1B: JP1.4, P1.1B (MOT-1B)
X-MOT-2A: JP1.2, P1.2A (MOT-2A)
X-MOT-2B: JP1.1, P1.2B (MOT-2B)
X-MS1: JP9.1, P1.MS1, R2.1
X-MS2: JP10.1, P1.MS2
X-MS3: JP11.1, P1.MS3
X-RESETSLEEP: P1.!RST (!RESET), P1.!SLP (!SLEEP)
X-STEP: IC2.51 (PA0_AD0), P1.STEP
X-STOP: IC2.15 (PB5_PCINT5_OC1A), JP27.1
XTAL1: IC2.24 (XTAL1), XTAL.1
XTAL2: IC2.23 (XTAL2), XTAL.2
Y-DIR: IC2.48 (PA3_AD3), P2.DIR
Y-MOT-1A: JP3.3, P2.1A (MOT-1A)
Y-MOT-1B: JP3.4, P2.1B (MOT-1B)
Y-MOT-2A: JP3.2, P2.2A (MOT-2A)
Y-MOT-2B: JP3.1, P2.2B (MOT-2B)
Y-MS1: JP12.1, P2.MS1, R3.1
Y-MS2: JP13.1, P2.MS2
Y-MS3: JP14.1, P2.MS3
Y-RESETSLEEP: P2.!RST (!RESET), P2.!SLP (!SLEEP)
Y-STEP: IC2.49 (PA2_AD2), P2.STEP
Y-STOP: IC2.16 (PB6_PCINT6_OC1B), JP28.1
Z-DIR: IC2.46 (PA5_AD5), P3.DIR
Z-MOT-1A: JP5.3, JP35.3, P3.1A (MOT-1A)
Z-MOT-1B: JP5.4, JP35.4, P3.1B (MOT-1B)
Z-MOT-2A: JP5.2, JP35.2, P3.2A (MOT-2A)
Z-MOT-2B: JP5.1, JP35.1, P3.2B (MOT-2B)
Z-MS1: JP15.1, P3.MS1, R4.1
Z-MS2: JP16.1, P3.MS2
Z-MS3: JP17.1, P3.MS3
Z-RESETSLEEP: P3.!RST (!RESET), P3.!SLP (!SLEEP)
Z-STEP: IC2.47 (PA4_AD4), P3.STEP
Z-STOP: IC2.17 (PB7_PCINT7_OC0A_OC1C), JP29.1

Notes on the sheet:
Motor Control X
Motor Control Y
Motor Control Z
Motor Control E
ISP
Thermistors
Endstops
Mosfets
Power Acc
Teensylu
Rev 0.9
Control for Reprap
Licensed under the Creative Commons Attributions ShareAlike 3.0 License
Extension Pin Headers
Power from ATX PS
Power from Screw Terminals & Vreg

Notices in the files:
TeensyluV1-2Layer/Teensylu-1.3a.brd:
Licensed CC-BY-SA
